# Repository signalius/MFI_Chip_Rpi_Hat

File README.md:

## MFI Raspberry Pi Hat
This Raspberry Pi HAT allows you to work with MFI chips with the symbols MFI343S00177 and MFI337S3959. 
Additionally, it has a USB C power in connector because USB C from Raspberry Pi may be needed as a USB OTG port.

* Tested on: Raspberry 5 and Zero 2W
* Interface: I2C

## Sample cert

Convert string hex to binary file
```bash
echo "3082025b06092a86...." | xxd -r -p > cert.bin
```

Decode it
```bash
openssl pkcs7 -inform DER -in cert.bin -print_certs -text -noout
```

Result
```bash
Certificate:
    Data:
        Version: 3 (0x2)
        Serial Number:
            22:22:aa:15:08:17:aa:06:aa:90:07:aa:16:78:09
        Signature Algorithm: sha1WithRSAEncryption
        Issuer: C=US, O=Apple Inc., OU=Apple Certification Authority, CN=Apple iPod Accessories Certification Authority
        Validity
            Not Before: Aug 17 20:46:29 2015 GMT
            Not After : Feb 14 22:18:08 2022 GMT
        Subject: C=US, O=Apple Inc., OU=Apple iPod Accessories, CN=IPA_2222AA150817AA06AA9007AA167809
        Subject Public Key Info:
            Public Key Algorithm: rsaEncryption
                Public-Key: (1024 bit)
                Modulus:
                    00:b7:dd:d3:81:e7:38:97:7c:06:72:91:3d:6c:4a:
                    cf:d0:01:d1:af:30:06:9c:05:67:84:76:da:bc:d5:
                    ee:94:8d:c4:63:11:3c:95:67:17:ff:a9:48:85:b8:
                    34:02:6e:8c:54:71:13:a7:c0:ad:11:39:86:4a:a1:
                    df:f3:45:d5:27:d5:e4:b2:b4:d0:61:ab:fb:31:7d:
                    f2:7c:c8:27:45:cd:d6:61:8d:88:d3:9f:43:a6:91:
                    3c:ad:ad:c5:1e:62:cc:61:1b:49:27:1a:10:26:a1:
                    20:14:a3:6b:58:62:ad:6a:bc:95:13:ac:72:38:73:
                    b2:84:e8:b6:51:a1:fa:39:2b
                Exponent: 65537 (0x10001)
        X509v3 extensions:
            X509v3 Subject Key Identifier: 
                D6:2B:D0:95:57:59:86:81:DB:D7:A0:32:75:2D:B9:A3:6E:5B:8A:38
            X509v3 Basic Constraints: critical
                CA:FALSE
            X509v3 Authority Key Identifier: 
                FF:4B:1A:43:9A:F5:19:96:AB:18:00:2B:61:C9:EE:40:9D:8E:C7:04
            X509v3 Key Usage: critical
                Digital Signature, Key Encipherment, Data Encipherment, Key Agreement
    Signature Algorithm: sha1WithRSAEncryption
    Signature Value:
        62:01:2d:2e:1b:39:ce:41:81:ea:a8:f3:07:e7:01:ee:d0:26:
```

## Schematic

# PCB view

## LICENSE
GNU General Public License v3.0

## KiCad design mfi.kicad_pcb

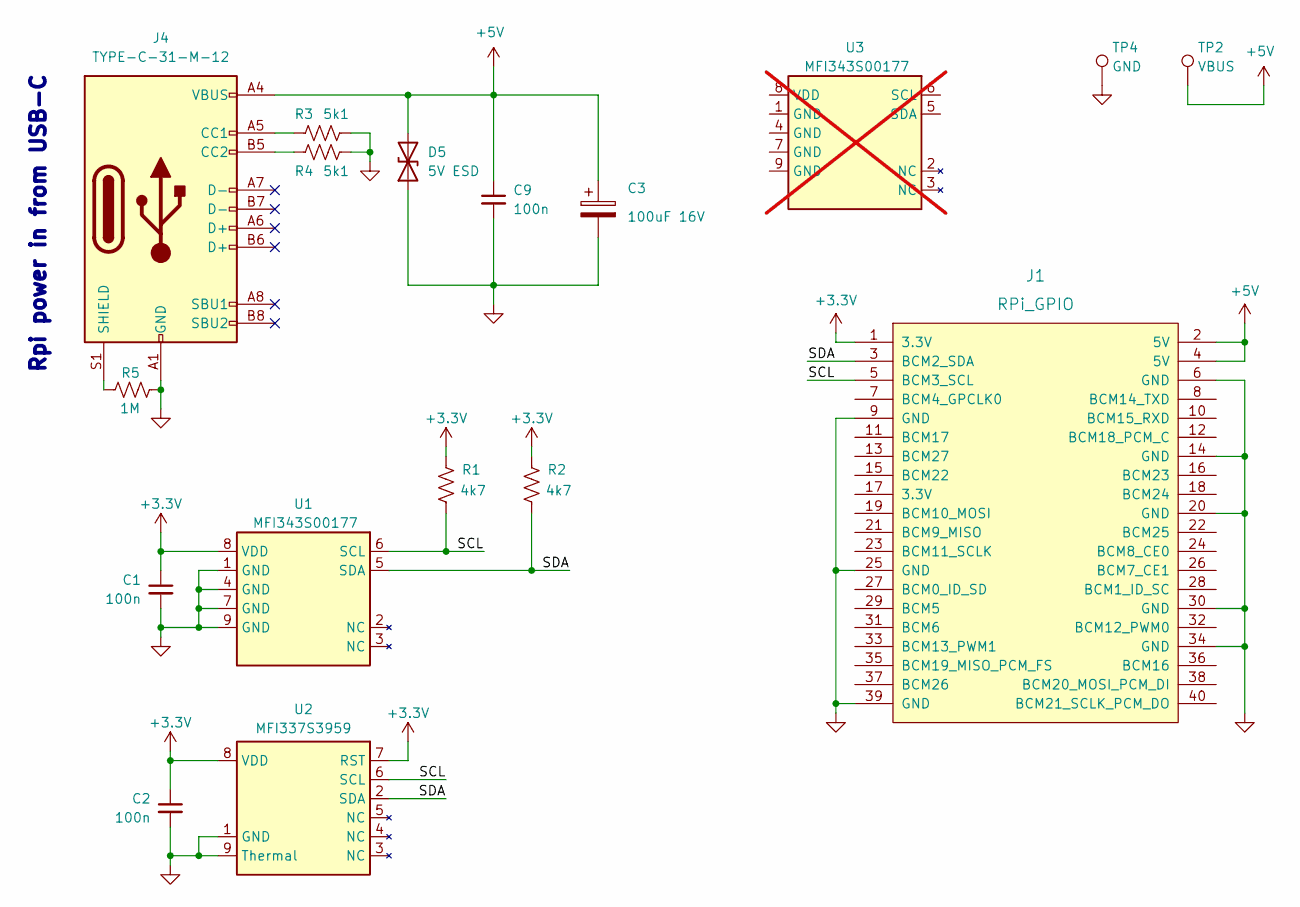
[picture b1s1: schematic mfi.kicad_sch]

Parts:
C1, C2, C9: 100n; C_0603_1608Metric
C3: 100uF 16V; CP_Radial_D10.0mm_P2.50mm_P5.00mm
D5: 5V ESD; D_SOD-323; MPN PESD5V0L1BA,115
J1: RPi_GPIO; PinHeader_2x20_P2.54mm_Vertical
J4: TYPE-C-31-M-12; USB_C_Receptacle_HRO_TYPE-C-31-M-12; MPN TYPE-C-31-M-12
R1, R2: 4k7; R_0603_1608Metric
R3, R4: 5k1; R_0603_1608Metric
R5: 1M; R_0603_1608Metric
TP2: VBUS; TestPoint_THTPad_1.5x1.5mm_Drill0.7mm
TP4: GND; TestPoint_THTPad_1.5x1.5mm_Drill0.7mm
U1: MFI343S00177; MFI_UDFN-8-1EP_2x3mm_P0.5mm
U2: MFI337S3959; MFI_WSON-8-1EP_2.5x2.5mm_P0.5mm
U3: MFI343S00177; MFI_UDFN-8-1EP_2x3mm_P0.5mm; not fitted

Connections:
+3.3V: C1.1, C2.1, J1.1 (3.3V), R1.1, R2.1, U1.8 (VDD), U2.7 (RST), U2.8 (VDD)
+5V: C3.1, C9.1, D5.2 (A2), J1.2 (5V), J1.4 (5V), J4.A4 (VBUS), J4.A9 (VBUS), J4.B4 (VBUS), J4.B9 (VBUS), TP2.1
/SCL: J1.5 (BCM3_SCL), R1.2, U1.6 (SCL), U2.6 (SCL)
/SDA: J1.3 (BCM2_SDA), R2.2, U1.5 (SDA), U2.2 (SDA)
GND: C1.2, C2.2, C3.2, C9.2, D5.1 (A1), J1.6 (GND), J1.9 (GND), J1.14 (GND), J1.20 (GND), J1.25 (GND), J1.30 (GND), J1.34 (GND), J1.39 (GND), J4.A1 (GND), J4.A12 (GND), J4.B1 (GND), J4.B12 (GND), R3.2, R4.2, R5.2, TP4.1, U1.1 (GND), U1.4 (GND), U1.7 (GND), U1.9 (GND), U2.1 (GND), U2.9 (Thermal)
unnamed: J4.A5 (CC1), R3.1
unnamed: J4.B5 (CC2), R4.1
unnamed: J4.S1 (SHIELD), R5.1

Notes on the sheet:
Rpi power in from USB-C

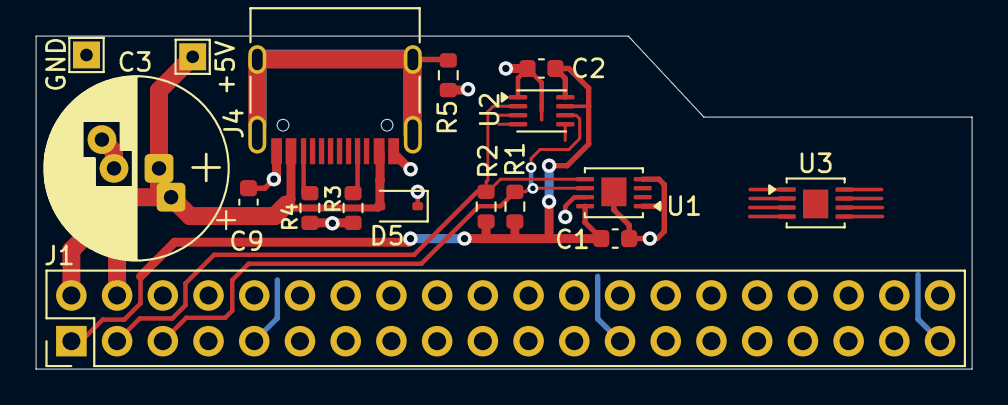
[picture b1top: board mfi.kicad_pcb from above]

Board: 2 copper layers, 52.0 x 18.5 mm, 17 parts (0 on the bottom side), 8 nets.

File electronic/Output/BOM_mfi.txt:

"Reference","Qty","Value","Footprint"
"C1,C2,C9","3","100n","Capacitor_SMD:C_0603_1608Metric"
"C3","1","470uF 16V","Capacitor_THT:CP_Radial_D10.0mm_P2.50mm_P5.00mm"
"D5","1","5V ESD","Diode_SMD:D_SOD-323"
"J1","1","RPi_GPIO","Connector_PinHeader_2.54mm:PinHeader_2x20_P2.54mm_Vertical"
"J4","1","TYPE-C-31-M-12","Connector_USB:USB_C_Receptacle_HRO_TYPE-C-31-M-12"
"R1,R2","2","4k7","Resistor_SMD:R_0603_1608Metric"
"R3,R4","2","5k1","Resistor_SMD:R_0603_1608Metric"
"R5","1","1M","Resistor_SMD:R_0603_1608Metric"
"TP2","1","VBUS","TestPoint:TestPoint_THTPad_1.5x1.5mm_Drill0.7mm"
"TP4","1","GND","TestPoint:TestPoint_THTPad_1.5x1.5mm_Drill0.7mm"
"U1","1","MFI343S00177","MFI:MFI_UDFN-8-1EP_2x3mm_P0.5mm"
"U2","1","MFI337S3959","MFI:MFI_WSON-8-1EP_2.5x2.5mm_P0.5mm"

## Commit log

2026-01-11 Initial
2026-01-14 Add app to read cert from mfi chip
2026-01-14 add gitignore
2026-01-14 Fix readme
2026-01-14 readme
2026-01-14 pcb.png
2026-01-14 Add bom
2026-01-14 refactor
2026-01-26 Add photos and new sample cert
2026-02-10 Auth app fix
2026-02-10 auth.py
2026-02-19 Add note to schematic
